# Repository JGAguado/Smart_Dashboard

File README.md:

[![Documentation Status][documentation-shield]][documentation]
[![GitHub Release][releases-shield]][releases]
[![License][license-shield]](LICENSE)

[![Project Maintenance][maintenance-shield]][maintenance]
[![BuyMeCoffee][buymecoffee-shield]][buymecoffee]

# Smart Dashboard
The Smart Dashboard is a platform to help display any kind of information on two kinds of ePaper display: the 7.5" black & white display and the 7.3" 7-colors display, both from Waveshare. It includes a BMP280 sensor for air temperature and pressure as well as all the electronics to work with the minimum power consumption, supporting solar charging.

## Project tree

<li><a href="./Design/">Design</a></li>
<li><a href="./Documentation/">Documentation</a></li>

<li><a href="./README.md">README.md</a></li>

[documentation-shield]: https://readthedocs.org/projects/smart-dashboard/badge/?version=latest&style=for-the-badge
[documentation]: https://smart-dashboard.readthedocs.io

[releases-shield]: https://img.shields.io/github/release/JGAguado/Smart_Dashboard.svg?style=for-the-badge
[releases]: https://github.com/JGAguado/Smart_Dashboard/releases

[license-shield]: https://img.shields.io/badge/License-CC%20BY--NC--SA%204.0-lightgrey.svg?style=for-the-badge

[maintenance-shield]: https://img.shields.io/badge/maintainer-J.%20G.%20Aguado-blue.svg?style=for-the-badge
[maintenance]: https://github.com/JGAguado

[buymecoffee-shield]: https://img.shields.io/badge/buy%20me%20a%20coffee-support-yellow.svg?style=for-the-badge
[buymecoffee]: https://www.buymeacoffee.com/J.G.Aguado

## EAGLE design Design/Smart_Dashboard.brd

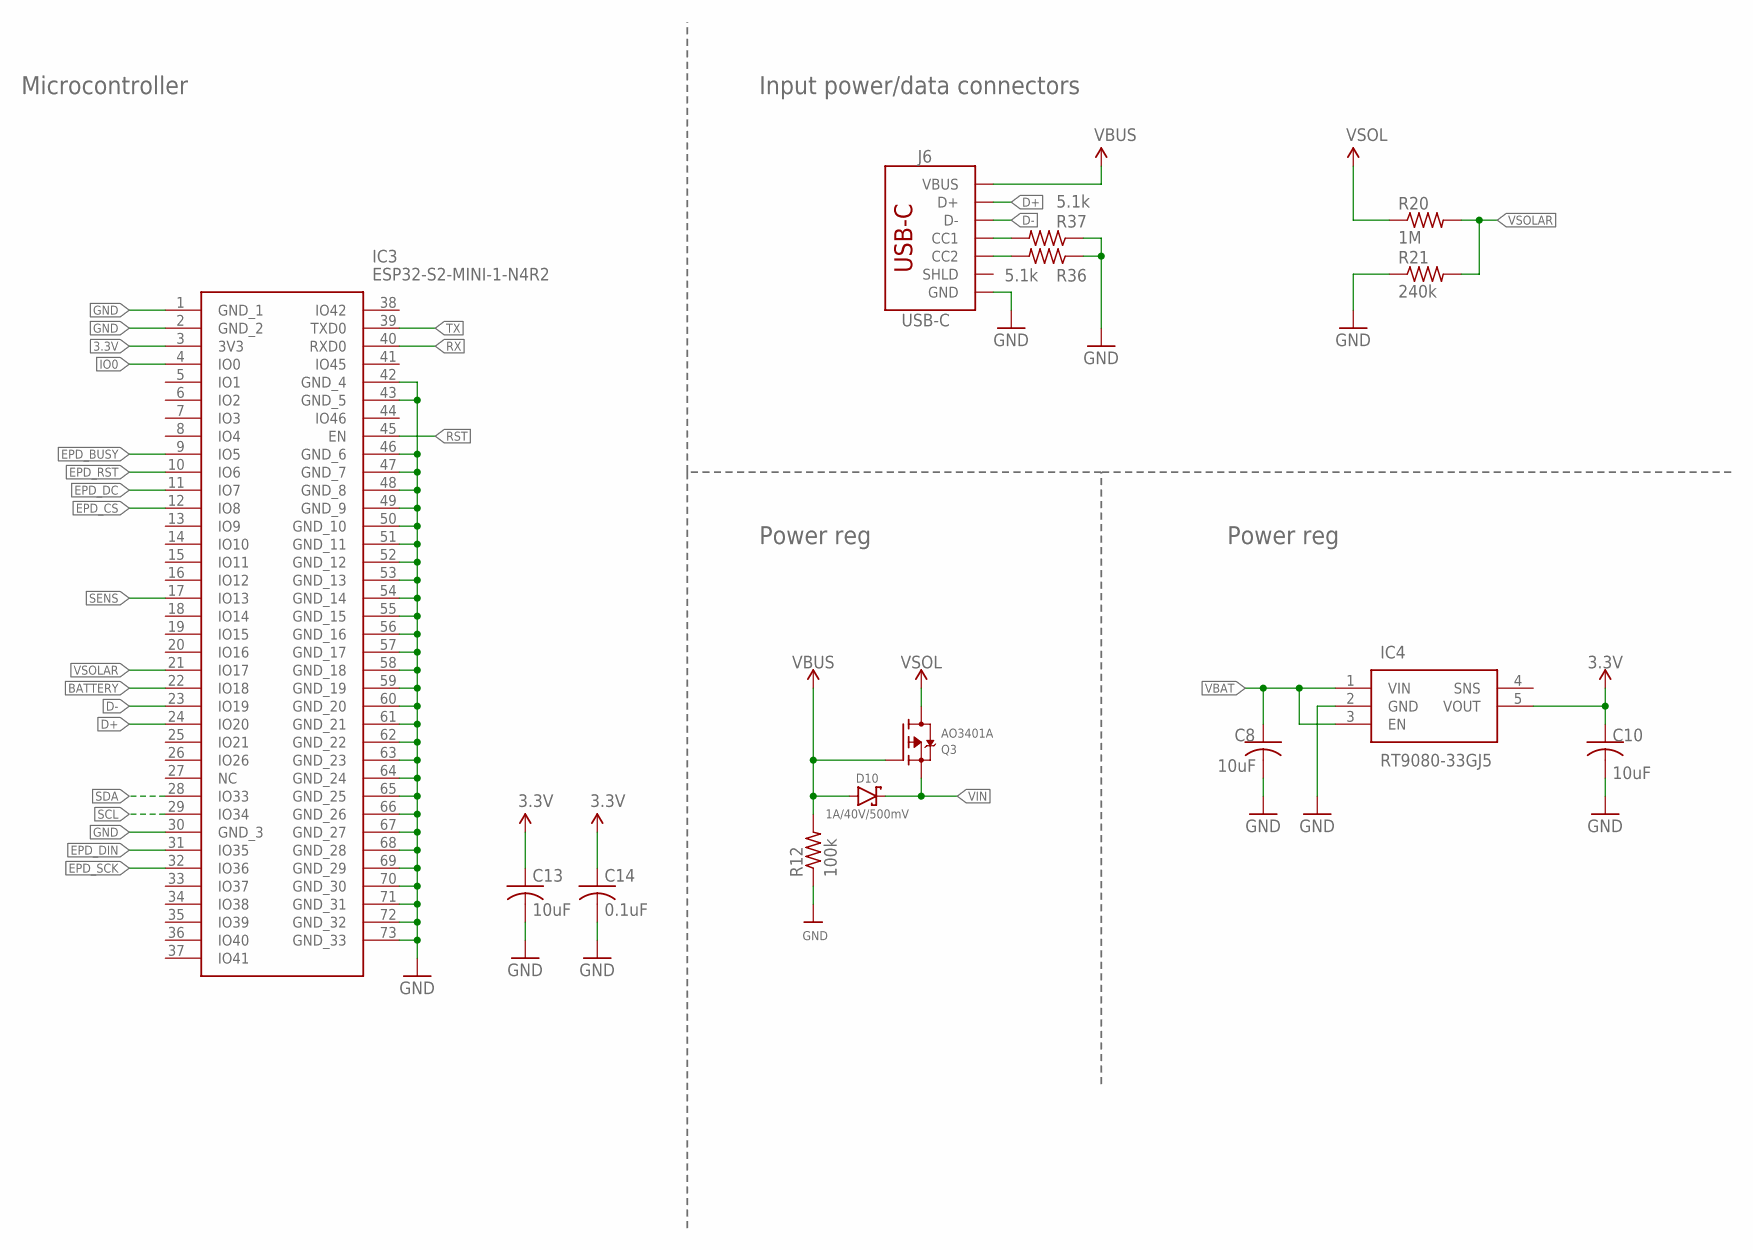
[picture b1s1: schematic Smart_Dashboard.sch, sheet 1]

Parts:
C8, C10, C13: 10uF; C0603
C14: 0.1uF; C0603
D10: 1A/40V/500mV; SMA-DIODE
IC3: ESP32-S2-MINI-1-N4R2; ESP32S2MINI1N4R2
IC4: RT9080-33GJ5; SOT94P280X100-5N; LCSC C841192
J6: USB-C; USB-C-16P-4LAYER-ISOLATED; LCSC C2765186
Q3: AO3401A; SOT23-R; LCSC C15127
R12: 100k; R0603
R20: 1M; R0603
R21: 240k; R0603
R36, R37: 5.1k; R0603

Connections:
3.3V: C10.1, C13.1, C14.1, IC3.3 (3V3), IC4.5 (VOUT); also elsewhere on the board
BATTERY: IC3.22 (IO18); also elsewhere on the board
CC3: J6.B5 (CC2), R36.2
CC4: J6.A5 (CC1), R37.2
D+: IC3.24 (IO20), J6.A6 (D+), J6.B6 (D+)
D-: IC3.23 (IO19), J6.A7 (D-), J6.B7 (D-)
EPD_BUSY: IC3.9 (IO5); also elsewhere on the board
EPD_CS: IC3.12 (IO8); also elsewhere on the board
EPD_DC: IC3.11 (IO7); also elsewhere on the board
EPD_DIN: IC3.31 (IO35); also elsewhere on the board
EPD_RST: IC3.10 (IO6); also elsewhere on the board
EPD_SCK: IC3.32 (IO36); also elsewhere on the board
GND: C8.2, C10.2, C13.2, C14.2, IC3.1 (GND_1), IC3.2 (GND_2), IC3.30 (GND_3), IC3.42 (GND_4), IC3.43 (GND_5), IC3.46 (GND_6), IC3.47 (GND_7), IC3.48 (GND_8), IC3.49 (GND_9), IC3.50 (GND_10), IC3.51 (GND_11), IC3.52 (GND_12), IC3.53 (GND_13), IC3.54 (GND_14), IC3.55 (GND_15), IC3.56 (GND_16), IC3.57 (GND_17), IC3.58 (GND_18), IC3.59 (GND_19), IC3.60 (GND_20), IC3.61 (GND_21), IC3.62 (GND_22), IC3.63 (GND_23), IC3.64 (GND_24), IC3.65 (GND_25), IC3.66 (GND_26), IC3.67 (GND_27), IC3.68 (GND_28), IC3.69 (GND_29), IC3.70 (GND_30), IC3.71 (GND_31), IC3.72 (GND_32), IC3.73 (GND_33), IC4.2 (GND), J6.GND, J6.GND2 (GND), R12.1, R21.1, R36.1, R37.1; also elsewhere on the board
IO0: IC3.4 (IO0); also elsewhere on the board
RST: IC3.45 (EN); also elsewhere on the board
RX: IC3.40 (RXD0); also elsewhere on the board
SCL: IC3.29 (IO34); also elsewhere on the board
SDA: IC3.28 (IO33); also elsewhere on the board
SENS: IC3.17 (IO13); also elsewhere on the board
TX: IC3.39 (TXD0); also elsewhere on the board
VBAT: C8.1, IC4.1 (VIN), IC4.3 (EN); also elsewhere on the board
VBUS: D10.A, J6.VBUS1 (VBUS), J6.VBUS2 (VBUS), Q3.1 (G), R12.2
VIN: D10.C, Q3.2 (S); also elsewhere on the board
VSOL: Q3.3 (D), R20.1
VSOLAR: IC3.21 (IO17), R20.2, R21.2

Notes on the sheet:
Microcontroller
Input power/data connectors
Power reg

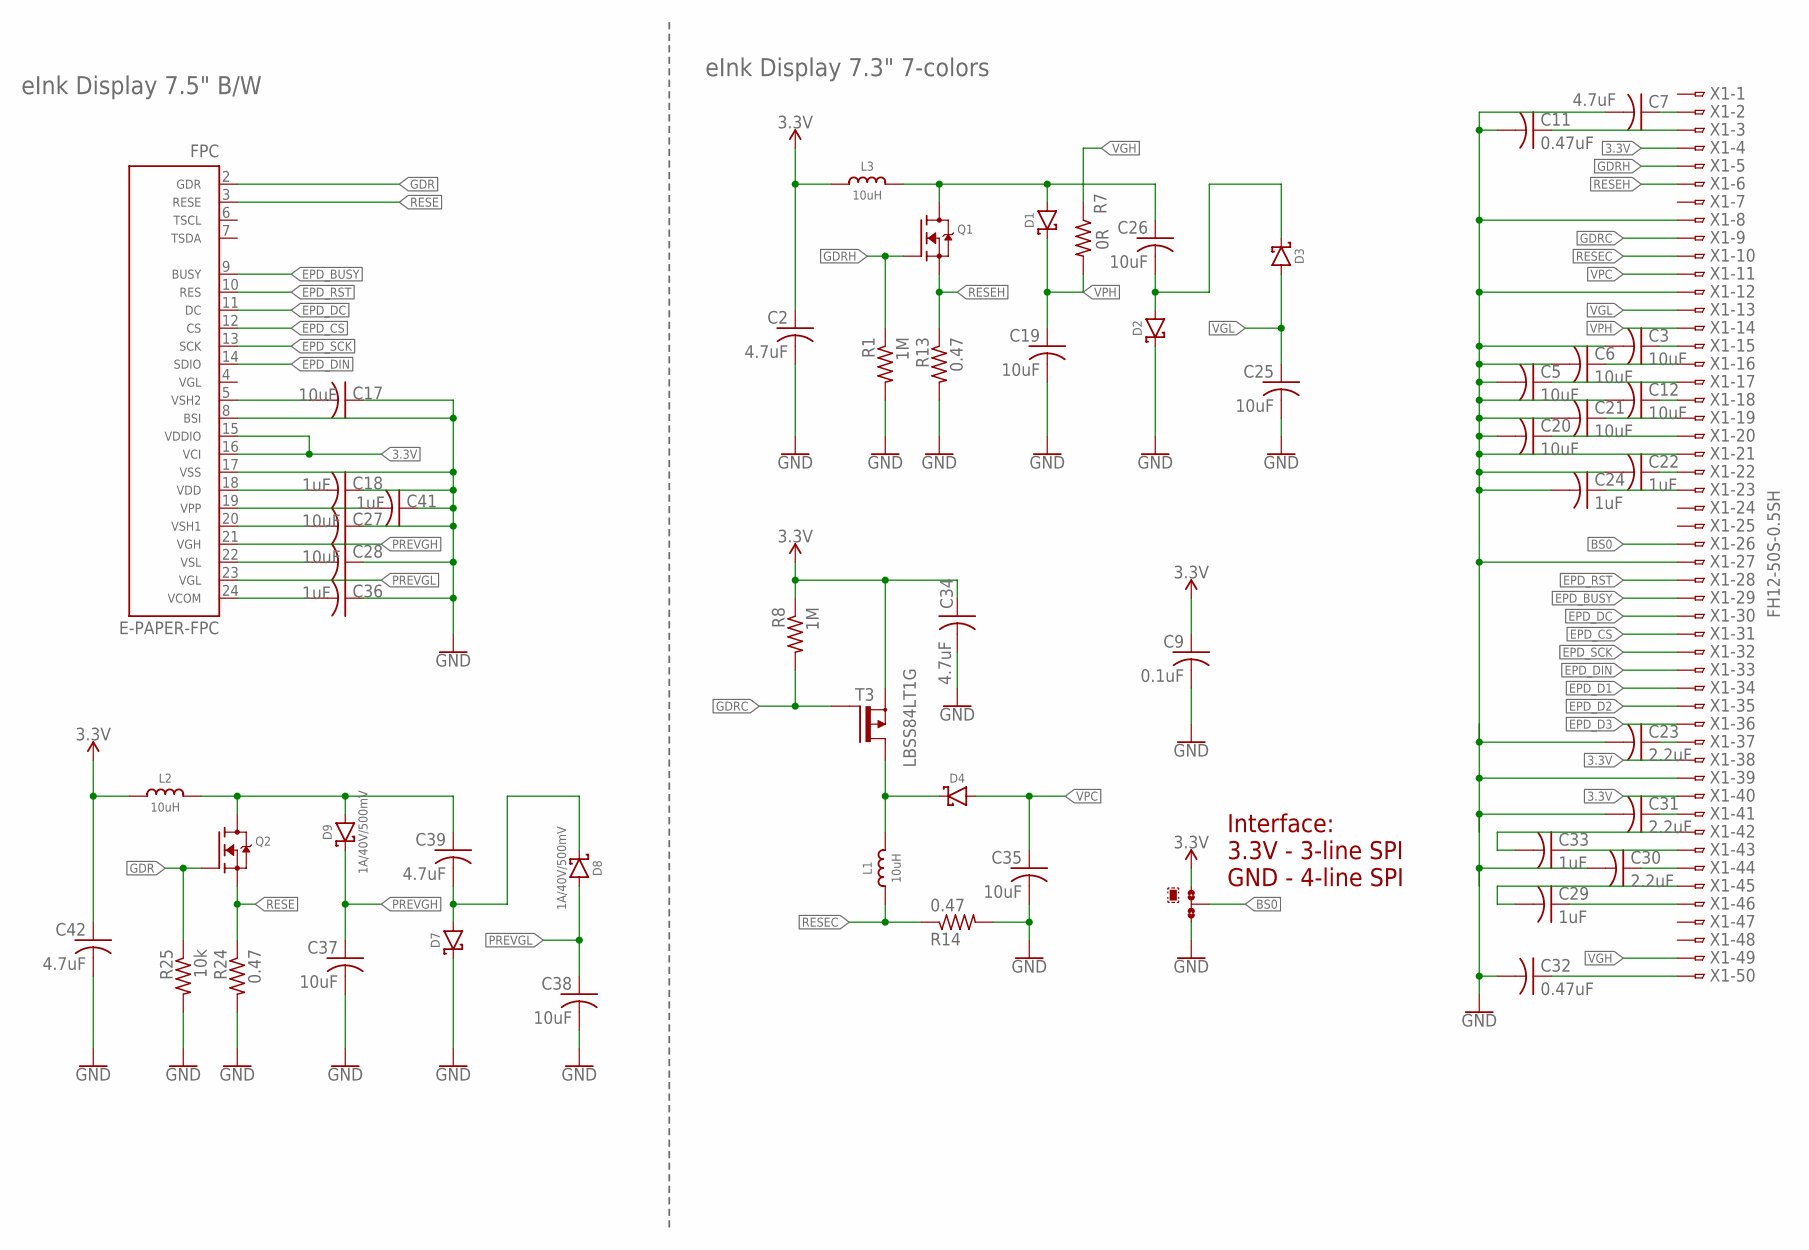
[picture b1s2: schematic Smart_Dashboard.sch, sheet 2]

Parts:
C2, C7, C34, C39, C42: 4.7uF; C0603
C3, C5, C6, C12, C17, C19, C20, C21, C25, C26, C27, C28, C35, C37, C38: 10uF; C0603
C9: 0.1uF; C0603
C11, C32: 0.47uF; C0603
C18, C22, C24, C29, C33, C36, C41: 1uF; C0603
C23, C30, C31: 2.2uF; C0603
D1, D2, D3, D4, D7, D8, D9: 1A/40V/500mV; SMA-DIODE
FPC: E-PAPER-FPC; FPC-05FB-24PH20
JMP1: 0R-JUMPA; A0R-JMP
L1, L2, L3: 10uH; INDUCTOR_4X4MM_NR401
Q1, Q2: IRLML0100; SOT23-3
R1, R8: 1M; R0603
R7: 0R; R0603
R13, R14, R24: 0.47; R0603
R25: 10k; R0603
T3: LBSS84LT1G; SOT23
X1: FH12-50S-0.5SH

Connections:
3.3V: C2.1, C9.1, C34.1, C42.1, FPC.15, FPC.16, JMP1.1, L2.P$2 (2), L3.P$2 (2), R8.1, T3.2 (S), X1.4, X1.38, X1.40; also elsewhere on the board
BS0: JMP1.2, X1.26
EPD_BUSY: FPC.9, X1.29; also elsewhere on the board
EPD_CS: FPC.12, X1.31; also elsewhere on the board
EPD_D1: X1.34
EPD_D2: X1.35
EPD_D3: X1.36
EPD_DC: FPC.11, X1.30; also elsewhere on the board
EPD_DIN: FPC.14, X1.33; also elsewhere on the board
EPD_RST: FPC.10, X1.28; also elsewhere on the board
EPD_SCK: FPC.13, X1.32; also elsewhere on the board
GDR: FPC.2, Q2.1 (G), R25.1
GDRC: R8.2, T3.1 (G), X1.9
GDRH: Q1.1 (G), R1.1, X1.5
GND: C2.2, C3.2, C5.2, C6.2, C7.2, C9.2, C11.2, C12.2, C17.1, C18.1, C19.2, C20.2, C21.2, C22.2, C23.2, C24.2, C25.2, C27.1, C28.1, C30.2, C31.2, C32.2, C34.2, C35.2, C36.1, C37.2, C38.2, C41.1, C42.2, D2.C, D7.C, FPC.8, FPC.17, JMP1.3, R1.2, R13.2, R14.2, R24.2, R25.2, X1.8, X1.12, X1.21, X1.27, X1.39; also elsewhere on the board
unnamed: C7.1, X1.2
unnamed: C3.1, X1.15
unnamed: C5.1, X1.17
unnamed: C17.2, FPC.5
unnamed: C18.2, FPC.18
unnamed: C27.2, FPC.20
unnamed: C26.2, D2.A, D3.C
unnamed: C26.1, D1.A, L3.P$1 (1), Q1.3 (D)
unnamed: C28.2, FPC.22
unnamed: C36.2, FPC.24
unnamed: C6.1, X1.16
unnamed: C11.1, X1.3
unnamed: C12.1, X1.18
unnamed: C20.1, X1.20
unnamed: C21.1, X1.19
unnamed: C22.1, X1.22
unnamed: C23.1, X1.37
unnamed: C24.1, X1.23
unnamed: C29.1, X1.46
unnamed: C29.2, X1.45
unnamed: C30.1, X1.44
unnamed: C31.1, X1.41
unnamed: C32.1, X1.50
unnamed: C33.1, X1.43
unnamed: C33.2, X1.42
unnamed: C39.2, D7.A, D8.C
unnamed: D4.C, L1.P$1 (1), T3.3 (D)
unnamed: C39.1, D9.A, L2.P$1 (1), Q2.3 (D)
unnamed: C41.2, FPC.19
PREVGH: C37.1, D9.C, FPC.21
PREVGL: C38.1, D8.A, FPC.23
RESE: FPC.3, Q2.2 (S), R24.1
RESEC: L1.P$2 (2), R14.1, X1.10
RESEH: Q1.2 (S), R13.1, X1.6
VGH: R7.1, X1.49
VGL: C25.1, D3.A, X1.13
VPC: C35.1, D4.A, X1.11
VPH: C19.1, D1.C, R7.2, X1.14

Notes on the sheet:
eInk Display 7.5" B/W
eInk Display 7.3" 7-colors
Interface: 3.3V - 3-line SPI GND - 4-line SPI

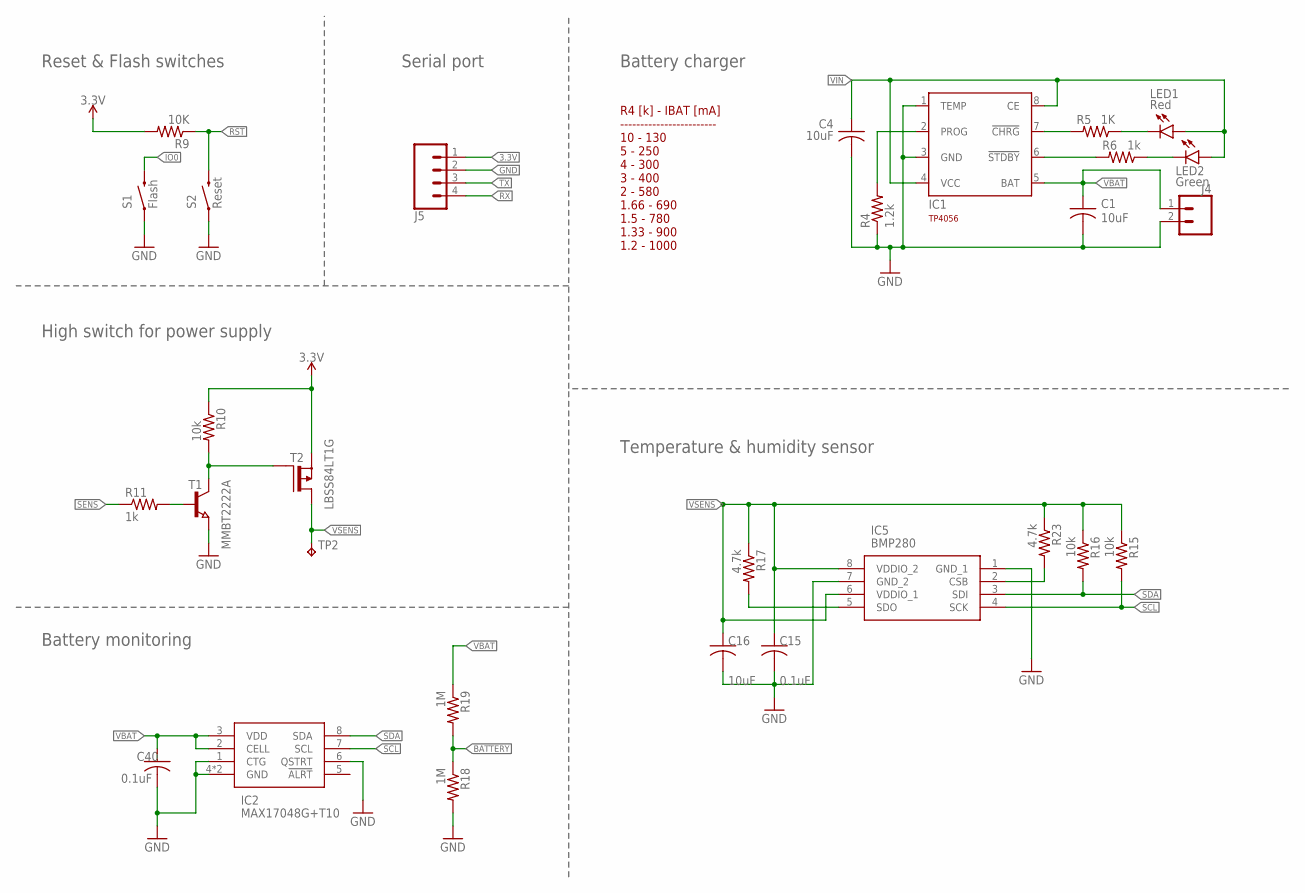
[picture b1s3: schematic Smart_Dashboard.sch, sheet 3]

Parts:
C1, C4, C16: 10uF; C0603
C15, C40: 0.1uF; C0603
IC1: TP4056; SOT23-8; LCSC C16581
IC2: MAX17048G+T10; SON50P200X200X80-9N
IC5: BMP280; 8-PIN-METAL-LID-LGA
J4: CONN_02-JST-2MM-SMT; JST-2-SMD; LCSC C3029440
J5: CONN_04PTH; 1X04
LED1: Red; LED_0603
LED2: Green; LED_0603
R4: 1.2k; R0603
R5: 1K; R0603
R6, R11: 1k; R0603
R9: 10K; R0603
R10, R15, R16: 10k; R0603
R17, R23: 4.7k; R0603
R18, R19: 1M; R0603
S1: Flash; TACTILE_SWITCH_SMD_5.2MM
S2: Reset; TACTILE_SWITCH_SMD_5.2MM
T1: MMBT2222A; SOT23
T2: LBSS84LT1G; SOT23
TP2: TPB1,27; B1,27

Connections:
3.3V: J5.1, R9.2, R10.1, T2.2 (S); also elsewhere on the board
BATTERY: R18.1, R19.2; also elsewhere on the board
GND: C1.2, C4.2, C15.2, C16.2, C40.2, IC1.1 (TEMP), IC1.3 (GND), IC2.1 (CTG), IC2.4 (GND), IC2.6 (QSTRT), IC2.9 (GND), IC5.1 (GND_1), IC5.7 (GND_2), J4.2 (1), J5.2, R4.1, R18.2, S1.1, S2.1, T1.2 (E); also elsewhere on the board
IO0: S1.3 (2); also elsewhere on the board
unnamed: IC1.6 (!STDBY), R6.2
unnamed: LED1.C, R5.1
unnamed: LED2.C, R6.1
unnamed: IC1.2 (PROG), R4.2
unnamed: IC1.7 (!CHRG), R5.2
unnamed: R10.2, T1.3 (C), T2.1 (G)
unnamed: IC5.5 (SDO), R17.2
unnamed: IC5.2 (CSB), R23.2
unnamed: R11.2, T1.1 (B)
RST: R9.1, S2.3 (2); also elsewhere on the board
RX: J5.4; also elsewhere on the board
SCL: IC2.7 (SCL), IC5.4 (SCK), R15.2; also elsewhere on the board
SDA: IC2.8 (SDA), IC5.3 (SDI), R16.2; also elsewhere on the board
SENS: R11.1; also elsewhere on the board
TX: J5.3; also elsewhere on the board
VBAT: C1.1, C40.1, IC1.5 (BAT), IC2.2 (CELL), IC2.3 (VDD), J4.1 (2), R19.1; also elsewhere on the board
VIN: C4.1, IC1.4 (VCC), IC1.8 (CE), LED1.A, LED2.A; also elsewhere on the board
VSENS: C15.1, C16.1, IC5.6 (VDDIO_1), IC5.8 (VDDIO_2), R15.1, R16.1, R17.1, R23.1, T2.3 (D), TP2.TP

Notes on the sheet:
High switch for power supply
Temperature & humidity sensor
Battery monitoring
R4 [k] - IBAT [mA] ------------------------ 10 - 130 5 - 250 4 - 300 3 - 400 2 - 580 1.66 - 690 1.5 - 780 1.33 - 900 1.2 - 1000
Battery charger
Reset & Flash switches
Serial port

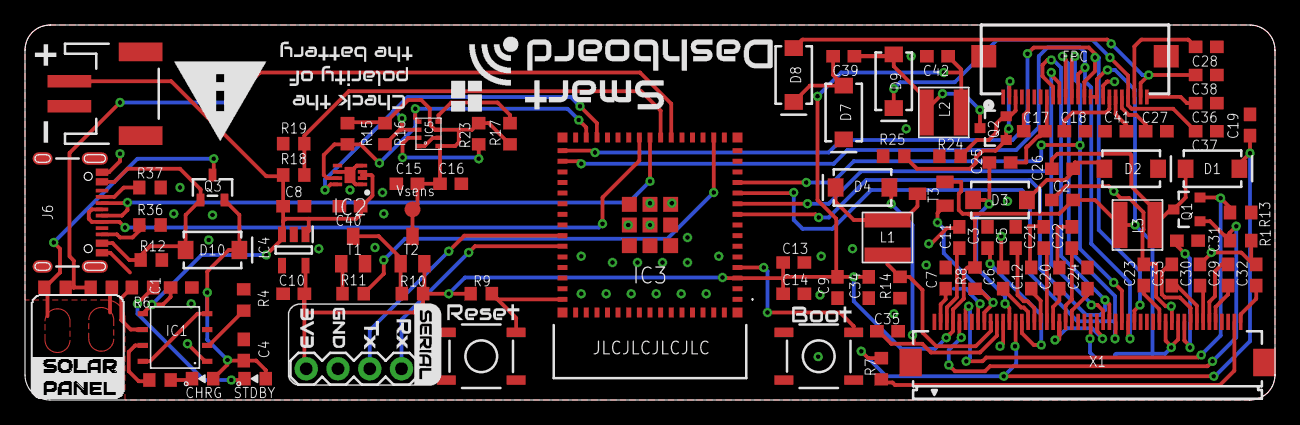
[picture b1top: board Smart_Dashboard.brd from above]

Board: 2 copper layers, 100.0 x 30.0 mm, 99 parts (1 on the bottom side), 77 nets.

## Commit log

2023-11-14 Added design files
2023-11-14 Added Documentation
2023-11-14 Added enclosure files
2023-11-14 docs

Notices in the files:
parts and their libraries:
microbuilder: This work is placed in the public domain, and may be freely used for commercial and non-commercial work with the following conditions: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
SparkFun-Connectors: Licensing: Creative Commons ShareAlike 4.0 International - https://creativecommons.org/licenses/by-sa/4.0
